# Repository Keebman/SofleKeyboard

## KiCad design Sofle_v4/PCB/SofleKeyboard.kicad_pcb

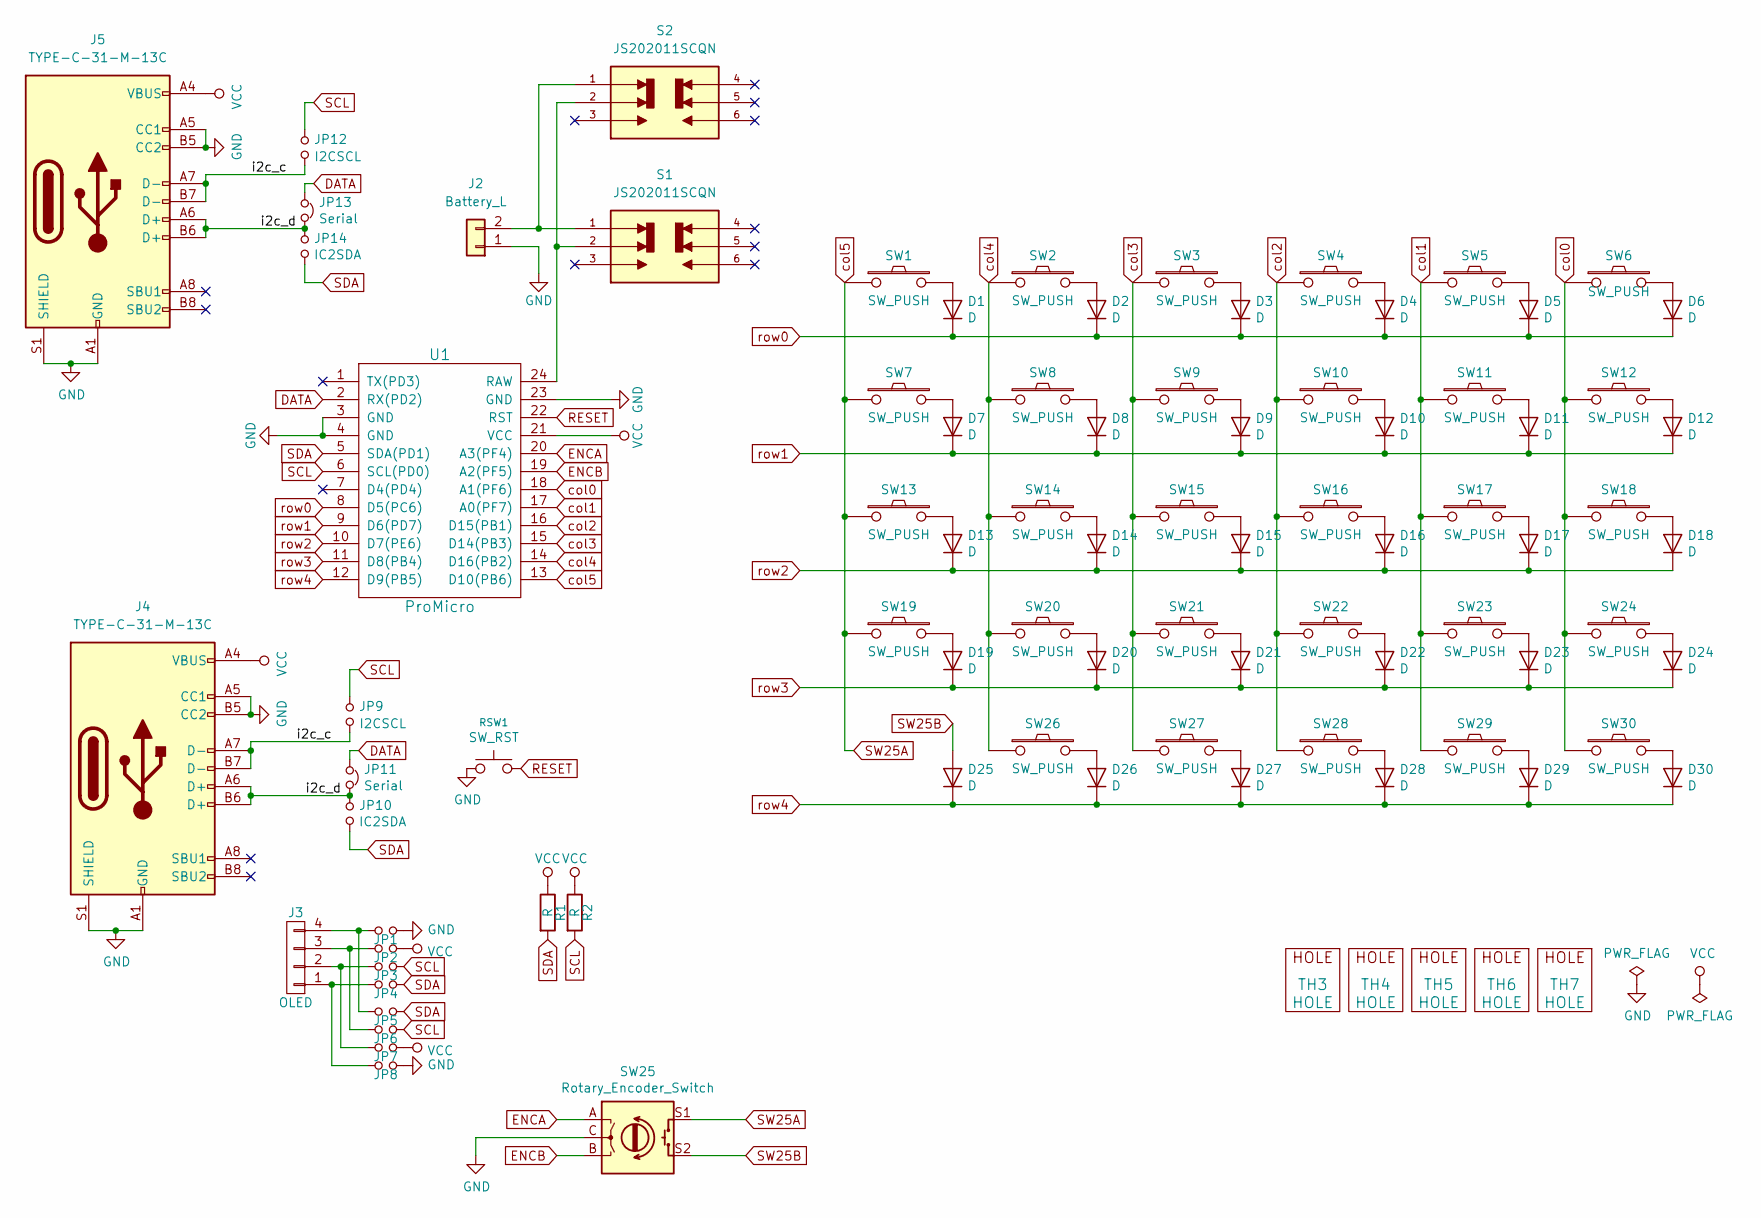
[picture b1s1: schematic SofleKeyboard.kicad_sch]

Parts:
D1, D2, D3, D4, D5, D6, D7, D8, D9, D10, D11, D12, D13, D14, D15, D16, D17, D18, D19, D20, D21, D22, D23, D24, D25, D26, D27, D28, D29, D30: D; Diode_SOD123
J2: Battery_L; PinHeader_1x02_P2.54mm_Vertical
J3: OLED; OLED_4Pin
J4, J5: TYPE-C-31-M-13C; JLCPCB Part # C2848620
JP1, JP2, JP3, JP4, JP5, JP6, JP7, JP8: Jumper_NO_Small; Jumper
JP9, JP12: I2CSCL; SolderJumper-2_P1.3mm_Open_TrianglePad1.0x1.5mm
JP10, JP14: IC2SDA; SolderJumper-2_P1.3mm_Open_TrianglePad1.0x1.5mm
JP11, JP13: Serial; SolderJumper-2_P1.3mm_Bridged2Bar_Pad1.0x1.5mm
R1, R2: R; R_1206_DoubleSided
RSW1: SW_RST; TACT_SWITCH_TVBP06
S1, S2: JS202011SCQN; SW_JS202011SCQN; PARTREV 26 May 22
SW1, SW2, SW3, SW4, SW5, SW6, SW7, SW8, SW9, SW10, SW11, SW12, SW13, SW14, SW15, SW16, SW17, SW18, SW19, SW20, SW21, SW22, SW23, SW24, SW27, SW28, SW29, SW30: SW_PUSH; CherryMX_Hotswap
SW25: Rotary_Encoder_Switch; RotaryEncoder_Alps_EC11E-Switch_Vertical_H20mm-keebio_modif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
SW26: SW_PUSH; CherryMX_Hotswap_1.5
TH3, TH4, TH5, TH6, TH7: HOLE; HOLE_M2_TH
U1: ProMicro; ArduinoProMicro-ZigZag-DoubleSided

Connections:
/i2c_c: J4.A7 (D-), J4.B7 (D-), J5.A7 (D-), J5.B7 (D-), JP9.2, JP12.2
/i2c_d: J4.A6 (D+), J4.B6 (D+), J5.A6 (D+), J5.B6 (D+), JP10.1, JP11.2, JP13.2, JP14.1
DATA: JP11.1, JP13.1, U1.2 (RX(PD2))
ENCA: SW25.A, U1.20 (A3(PF4))
ENCB: SW25.B, U1.19 (A2(PF5))
GND: J2.1, J4.A1 (GND), J4.A5 (CC1), J4.A12 (GND), J4.B1 (GND), J4.B5 (CC2), J4.B12 (GND), J4.S1 (SHIELD), J5.A1 (GND), J5.A5 (CC1), J5.A12 (GND), J5.B1 (GND), J5.B5 (CC2), J5.B12 (GND), J5.S1 (SHIELD), JP1.2, JP8.2, RSW1.1, SW25.C, U1.3 (GND), U1.4 (GND), U1.23 (GND)
unnamed: D1.2 (A), SW1.2
unnamed: D2.2 (A), SW2.2
unnamed: D3.2 (A), SW3.2
unnamed: D4.2 (A), SW4.2
unnamed: D5.2 (A), SW5.2
unnamed: D6.2 (A), SW6.2
unnamed: D7.2 (A), SW7.2
unnamed: D8.2 (A), SW8.2
unnamed: D9.2 (A), SW9.2
unnamed: D10.2 (A), SW10.2
unnamed: D11.2 (A), SW11.2
unnamed: D12.2 (A), SW12.2
unnamed: D13.2 (A), SW13.2
unnamed: D14.2 (A), SW14.2
unnamed: D15.2 (A), SW15.2
unnamed: D16.2 (A), SW16.2
unnamed: D17.2 (A), SW17.2
unnamed: D18.2 (A), SW18.2
unnamed: D19.2 (A), SW19.2
unnamed: D20.2 (A), SW20.2
unnamed: D21.2 (A), SW21.2
unnamed: D22.2 (A), SW22.2
unnamed: D23.2 (A), SW23.2
unnamed: D24.2 (A), SW24.2
unnamed: D26.2 (A), SW26.2
unnamed: D27.2 (A), SW27.2
unnamed: D28.2 (A), SW28.2
unnamed: D29.2 (A), SW29.2
unnamed: D30.2 (A), SW30.2
unnamed: J2.2, S1.1, S2.1
unnamed: J3.1, JP4.1, JP8.1
unnamed: J3.2, JP3.1, JP7.1
unnamed: J3.3, JP2.1, JP6.1
unnamed: J3.4, JP1.1, JP5.1
unnamed: S1.2, S2.2, U1.24 (RAW)
RESET: RSW1.2, U1.22 (RST)
SCL: JP3.2, JP6.2, JP9.1, JP12.1, R2.2, U1.6 (SCL(PD0))
SDA: JP4.2, JP5.2, JP10.2, JP14.2, R1.2, U1.5 (SDA(PD1))
SW25A: SW1.1, SW7.1, SW13.1, SW19.1, SW25.S1, U1.13 (D10(PB6))
SW25B: D25.2 (A), SW25.S2
VCC: J4.A4 (VBUS), J4.A9 (VBUS), J4.B4 (VBUS), J4.B9 (VBUS), J5.A4 (VBUS), J5.A9 (VBUS), J5.B4 (VBUS), J5.B9 (VBUS), JP2.2, JP7.2, R1.1, R2.1, U1.21 (VCC)
col0: SW6.1, SW12.1, SW18.1, SW24.1, SW30.1, U1.18 (A1(PF6))
col1: SW5.1, SW11.1, SW17.1, SW23.1, SW29.1, U1.17 (A0(PF7))
col2: SW4.1, SW10.1, SW16.1, SW22.1, SW28.1, U1.16 (D15(PB1))
col3: SW3.1, SW9.1, SW15.1, SW21.1, SW27.1, U1.15 (D14(PB3))
col4: SW2.1, SW8.1, SW14.1, SW20.1, SW26.1, U1.14 (D16(PB2))
row0: D1.1 (K), D2.1 (K), D3.1 (K), D4.1 (K), D5.1 (K), D6.1 (K), U1.8 (D5(PC6))
row1: D7.1 (K), D8.1 (K), D9.1 (K), D10.1 (K), D11.1 (K), D12.1 (K), U1.9 (D6(PD7))
row2: D13.1 (K), D14.1 (K), D15.1 (K), D16.1 (K), D17.1 (K), D18.1 (K), U1.10 (D7(PE6))
row3: D19.1 (K), D20.1 (K), D21.1 (K), D22.1 (K), D23.1 (K), D24.1 (K), U1.11 (D8(PB4))
row4: D25.1 (K), D26.1 (K), D27.1 (K), D28.1 (K), D29.1 (K), D30.1 (K), U1.12 (D9(PB5))

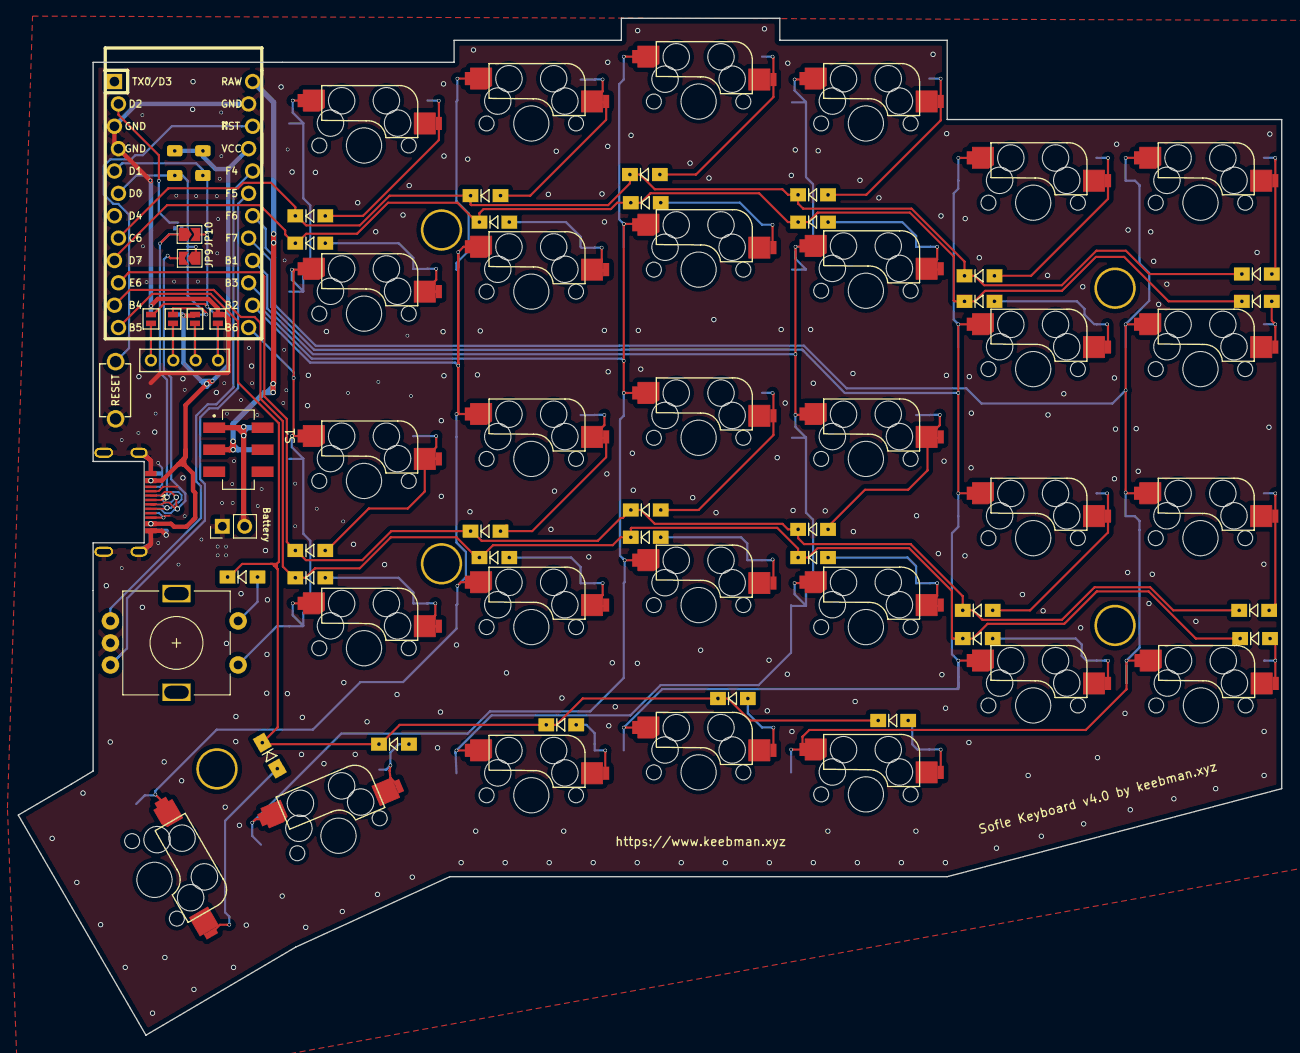
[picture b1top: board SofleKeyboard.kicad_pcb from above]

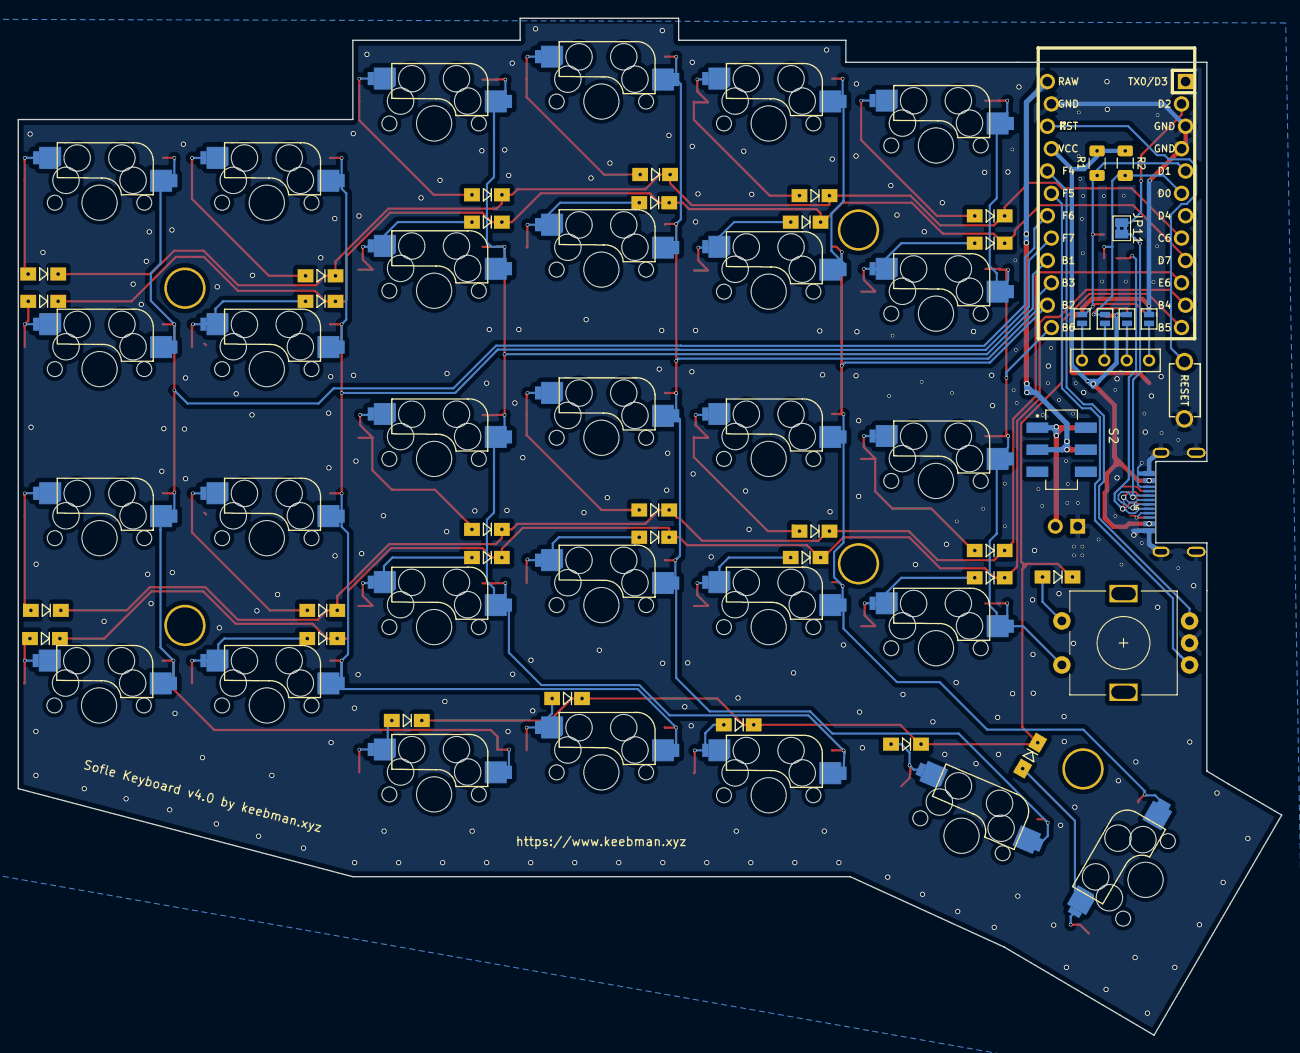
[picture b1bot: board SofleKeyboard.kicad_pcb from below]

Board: 2 copper layers, 143.5 x 115.5 mm, 86 parts (9 on the bottom side), 57 nets.

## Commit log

2025-03-10 Sofle v3: replaced TRC with USB-C. Generated Gerber and Drill files
2025-03-22 Sofle v4 added
